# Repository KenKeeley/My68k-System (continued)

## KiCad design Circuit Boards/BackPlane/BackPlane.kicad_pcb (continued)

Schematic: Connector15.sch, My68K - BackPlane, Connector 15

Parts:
J15: DIN41612-C-96-F; Part No. 1656359
JP27, JP28: Jumper; Part No. 1593411

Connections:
+3V3: J15.A31, J15.B31, J15.C31; also elsewhere on the board
+5V: J15.A32, J15.B32, J15.C32; also elsewhere on the board
A00: J15.A23; also elsewhere on the board
A01: J15.A24; also elsewhere on the board
A02: J15.A25; also elsewhere on the board
A03: J15.A26; also elsewhere on the board
A04: J15.A27; also elsewhere on the board
A05: J15.A28; also elsewhere on the board
A06: J15.A29; also elsewhere on the board
A07: J15.A30; also elsewhere on the board
A08: J15.C23; also elsewhere on the board
A09: J15.C24; also elsewhere on the board
A10: J15.C25; also elsewhere on the board
A11: J15.C26; also elsewhere on the board
A12: J15.C27; also elsewhere on the board
A13: J15.C28; also elsewhere on the board
A14: J15.C29; also elsewhere on the board
A15: J15.C30; also elsewhere on the board
A16: J15.C11; also elsewhere on the board
A17: J15.C12; also elsewhere on the board
A18: J15.C13; also elsewhere on the board
A19: J15.C14; also elsewhere on the board
A20: J15.C15; also elsewhere on the board
A21: J15.C16; also elsewhere on the board
A22: J15.C17; also elsewhere on the board
A23: J15.C18; also elsewhere on the board
A24: J15.C19; also elsewhere on the board
A25: J15.A13; also elsewhere on the board
A26: J15.A14; also elsewhere on the board
A27: J15.A15; also elsewhere on the board
A28: J15.A16; also elsewhere on the board
A29: J15.A17; also elsewhere on the board
A30: J15.A18; also elsewhere on the board
A31: J15.A19; also elsewhere on the board
AS: J15.B9; also elsewhere on the board
BGACK: J15.A22; also elsewhere on the board
BGOUT14: J15.A20, JP27.1; also elsewhere on the board
BGOUT15: J15.A21, JP27.2; also elsewhere on the board
BR: J15.C22; also elsewhere on the board
D00: J15.A1; also elsewhere on the board
D01: J15.A2; also elsewhere on the board
D02: J15.A3; also elsewhere on the board
D03: J15.A4; also elsewhere on the board
D04: J15.A5; also elsewhere on the board
D05: J15.A6; also elsewhere on the board
D06: J15.A7; also elsewhere on the board
D07: J15.A8; also elsewhere on the board
D08: J15.C1; also elsewhere on the board
D09: J15.C2; also elsewhere on the board
D10: J15.C3; also elsewhere on the board
D11: J15.C4; also elsewhere on the board
D12: J15.C5; also elsewhere on the board
D13: J15.C6; also elsewhere on the board
D14: J15.C7; also elsewhere on the board
D15: J15.C8; also elsewhere on the board
D16: J15.B1; also elsewhere on the board
D17: J15.B2; also elsewhere on the board
D18: J15.B3; also elsewhere on the board
D19: J15.B4; also elsewhere on the board
D20: J15.B5; also elsewhere on the board
D21: J15.B6; also elsewhere on the board
D22: J15.B7; also elsewhere on the board
D23: J15.B8; also elsewhere on the board
D24: J15.B11; also elsewhere on the board
D25: J15.B12; also elsewhere on the board
D26: J15.B13; also elsewhere on the board
D27: J15.B14; also elsewhere on the board
D28: J15.B15; also elsewhere on the board
D29: J15.B16; also elsewhere on the board
D30: J15.B17; also elsewhere on the board
D31: J15.B18; also elsewhere on the board
DSACK0: J15.B22; also elsewhere on the board
DSACK1: J15.B23; also elsewhere on the board
GND: J15.33 (GND), J15.34 (GND), J15.A10, J15.B10, J15.C10; also elsewhere on the board
IACKOUT14: J15.B20, JP28.1; also elsewhere on the board
IACKOUT15: J15.B21, JP28.2; also elsewhere on the board
ID: J15.C21; also elsewhere on the board
IRQ1: J15.B30; also elsewhere on the board
IRQ2: J15.B29; also elsewhere on the board
IRQ3: J15.B28; also elsewhere on the board
IRQ4: J15.B27; also elsewhere on the board
IRQ5: J15.B26; also elsewhere on the board
IRQ6: J15.B25; also elsewhere on the board
IRQ7: J15.B24; also elsewhere on the board
SIZ0: J15.A11; also elsewhere on the board
SIZ1: J15.A12; also elsewhere on the board
STERM: J15.B19; also elsewhere on the board
SYSHALT: J15.C20; also elsewhere on the board
SYSRESET: J15.C9; also elsewhere on the board
WRITE: J15.A9; also elsewhere on the board

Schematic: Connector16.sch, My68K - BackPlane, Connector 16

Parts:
J16: DIN41612-C-96-F; Part No. 1656359

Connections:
+3V3: J16.A31, J16.B31, J16.C31; also elsewhere on the board
+5V: J16.A32, J16.B32, J16.C32; also elsewhere on the board
A00: J16.A23; also elsewhere on the board
A01: J16.A24; also elsewhere on the board
A02: J16.A25; also elsewhere on the board
A03: J16.A26; also elsewhere on the board
A04: J16.A27; also elsewhere on the board
A05: J16.A28; also elsewhere on the board
A06: J16.A29; also elsewhere on the board
A07: J16.A30; also elsewhere on the board
A08: J16.C23; also elsewhere on the board
A09: J16.C24; also elsewhere on the board
A10: J16.C25; also elsewhere on the board
A11: J16.C26; also elsewhere on the board
A12: J16.C27; also elsewhere on the board
A13: J16.C28; also elsewhere on the board
A14: J16.C29; also elsewhere on the board
A15: J16.C30; also elsewhere on the board
A16: J16.C11; also elsewhere on the board
A17: J16.C12; also elsewhere on the board
A18: J16.C13; also elsewhere on the board
A19: J16.C14; also elsewhere on the board
A20: J16.C15; also elsewhere on the board
A21: J16.C16; also elsewhere on the board
A22: J16.C17; also elsewhere on the board
A23: J16.C18; also elsewhere on the board
A24: J16.C19; also elsewhere on the board
A25: J16.A13; also elsewhere on the board
A26: J16.A14; also elsewhere on the board
A27: J16.A15; also elsewhere on the board
A28: J16.A16; also elsewhere on the board
A29: J16.A17; also elsewhere on the board
A30: J16.A18; also elsewhere on the board
A31: J16.A19; also elsewhere on the board
AS: J16.B9; also elsewhere on the board
BGACK: J16.A22; also elsewhere on the board
BGOUT15: J16.A20; also elsewhere on the board
BR: J16.C22; also elsewhere on the board
D00: J16.A1; also elsewhere on the board
D01: J16.A2; also elsewhere on the board
D02: J16.A3; also elsewhere on the board
D03: J16.A4; also elsewhere on the board
D04: J16.A5; also elsewhere on the board
D05: J16.A6; also elsewhere on the board
D06: J16.A7; also elsewhere on the board
D07: J16.A8; also elsewhere on the board
D08: J16.C1; also elsewhere on the board
D09: J16.C2; also elsewhere on the board
D10: J16.C3; also elsewhere on the board
D11: J16.C4; also elsewhere on the board
D12: J16.C5; also elsewhere on the board
D13: J16.C6; also elsewhere on the board
D14: J16.C7; also elsewhere on the board
D15: J16.C8; also elsewhere on the board
D16: J16.B1; also elsewhere on the board
D17: J16.B2; also elsewhere on the board
D18: J16.B3; also elsewhere on the board
D19: J16.B4; also elsewhere on the board
D20: J16.B5; also elsewhere on the board
D21: J16.B6; also elsewhere on the board
D22: J16.B7; also elsewhere on the board
D23: J16.B8; also elsewhere on the board
D24: J16.B11; also elsewhere on the board
D25: J16.B12; also elsewhere on the board
D26: J16.B13; also elsewhere on the board
D27: J16.B14; also elsewhere on the board
D28: J16.B15; also elsewhere on the board
D29: J16.B16; also elsewhere on the board
D30: J16.B17; also elsewhere on the board
D31: J16.B18; also elsewhere on the board
DSACK0: J16.B22; also elsewhere on the board
DSACK1: J16.B23; also elsewhere on the board
GND: J16.33 (GND), J16.34 (GND), J16.A10, J16.B10, J16.C10; also elsewhere on the board
IACKOUT15: J16.B20; also elsewhere on the board
ID: J16.C21; also elsewhere on the board
IRQ1: J16.B30; also elsewhere on the board
IRQ2: J16.B29; also elsewhere on the board
IRQ3: J16.B28; also elsewhere on the board
IRQ4: J16.B27; also elsewhere on the board
IRQ5: J16.B26; also elsewhere on the board
IRQ6: J16.B25; also elsewhere on the board
IRQ7: J16.B24; also elsewhere on the board
SIZ0: J16.A11; also elsewhere on the board
SIZ1: J16.A12; also elsewhere on the board
STERM: J16.B19; also elsewhere on the board
SYSHALT: J16.C20; also elsewhere on the board
SYSRESET: J16.C9; also elsewhere on the board
WRITE: J16.A9; also elsewhere on the board

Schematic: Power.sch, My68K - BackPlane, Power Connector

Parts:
J17: 4771 3-pin; 4771_3-pin; Part No. P5603
J18: DIN41612-H-15-F; Part No. 1656221

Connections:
+3V3: J18.D18 (3v), J18.Z16 (3v), J18.Z20 (3v); also elsewhere on the board
+5V: J18.D26 (5v), J18.Z24 (5v), J18.Z28 (5v); also elsewhere on the board
GND: J17.2, J18.33 (GND), J18.34 (GND), J18.D6 (GND), J18.D10 (GND), J18.D14 (GND), J18.D22 (GND), J18.D30 (GND); also elsewhere on the board
unnamed: J17.1, J18.Z8 (AC-L)
unnamed: J17.3, J18.Z4 (AC-N)
VTT: J18.Z12 (Vterm), J18.Z32 (Vterm); also elsewhere on the board

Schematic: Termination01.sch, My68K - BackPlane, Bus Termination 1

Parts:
C1, C2, C3: 39uF; CP_Radial_6.3x11x2.5; Part No. 2465934
RP1, RP2, RP3, RP4, RP5, RP6, RP7, RP8, RP9: 270; SIP_10; Part No. 1612547

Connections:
A00: RP7.3; also elsewhere on the board
A01: RP7.4; also elsewhere on the board
A02: RP7.5; also elsewhere on the board
A03: RP7.6; also elsewhere on the board
A04: RP7.7; also elsewhere on the board
A05: RP7.8; also elsewhere on the board
A06: RP7.9; also elsewhere on the board
A07: RP7.10; also elsewhere on the board
A08: RP9.3; also elsewhere on the board
A09: RP9.4; also elsewhere on the board
A10: RP9.5; also elsewhere on the board
A11: RP9.6; also elsewhere on the board
A12: RP9.7; also elsewhere on the board
A13: RP9.8; also elsewhere on the board
A14: RP9.9; also elsewhere on the board
A15: RP9.10; also elsewhere on the board
A16: RP6.10; also elsewhere on the board
A17: RP6.9; also elsewhere on the board
A18: RP6.8; also elsewhere on the board
A19: RP6.7; also elsewhere on the board
A20: RP6.6; also elsewhere on the board
A21: RP6.5; also elsewhere on the board
A22: RP6.4; also elsewhere on the board
A23: RP6.3; also elsewhere on the board
A24: RP6.2; also elsewhere on the board
A25: RP4.8; also elsewhere on the board
A26: RP4.7; also elsewhere on the board
A27: RP4.6; also elsewhere on the board
A28: RP4.5; also elsewhere on the board
A29: RP4.4; also elsewhere on the board
A30: RP4.3; also elsewhere on the board
A31: RP4.2; also elsewhere on the board
AS: RP2.10; also elsewhere on the board
BGACK: RP7.2; also elsewhere on the board
BR: RP9.2; also elsewhere on the board
D00: RP1.2; also elsewhere on the board
D01: RP1.3; also elsewhere on the board
D02: RP1.4; also elsewhere on the board
D03: RP1.5; also elsewhere on the board
D04: RP1.6; also elsewhere on the board
D05: RP1.7; also elsewhere on the board
D06: RP1.8; also elsewhere on the board
D07: RP1.9; also elsewhere on the board
D08: RP3.2; also elsewhere on the board
D09: RP3.3; also elsewhere on the board
D10: RP3.4; also elsewhere on the board
D11: RP3.5; also elsewhere on the board
D12: RP3.6; also elsewhere on the board
D13: RP3.7; also elsewhere on the board
D14: RP3.8; also elsewhere on the board
D15: RP3.9; also elsewhere on the board
D16: RP2.2; also elsewhere on the board
D17: RP2.3; also elsewhere on the board
D18: RP2.4; also elsewhere on the board
D19: RP2.5; also elsewhere on the board
D20: RP2.6; also elsewhere on the board
D21: RP2.7; also elsewhere on the board
D22: RP2.8; also elsewhere on the board
D23: RP2.9; also elsewhere on the board
D24: RP5.10; also elsewhere on the board
D25: RP5.9; also elsewhere on the board
D26: RP5.8; also elsewhere on the board
D27: RP5.7; also elsewhere on the board
D28: RP5.6; also elsewhere on the board
D29: RP5.5; also elsewhere on the board
D30: RP5.4; also elsewhere on the board
D31: RP5.3; also elsewhere on the board
DSACK0: RP8.2; also elsewhere on the board
DSACK1: RP8.3; also elsewhere on the board
GND: C1.2, C2.2, C3.2; also elsewhere on the board
IRQ1: RP8.10; also elsewhere on the board
IRQ2: RP8.9; also elsewhere on the board
IRQ3: RP8.8; also elsewhere on the board
IRQ4: RP8.7; also elsewhere on the board
IRQ5: RP8.6; also elsewhere on the board
IRQ6: RP8.5; also elsewhere on the board
IRQ7: RP8.4; also elsewhere on the board
SIZ0: RP4.10; also elsewhere on the board
SIZ1: RP4.9; also elsewhere on the board
STERM: RP5.2; also elsewhere on the board
SYSRESET: RP3.10; also elsewhere on the board
VTT: C1.1, C2.1, C3.1, RP1.1 (COM), RP2.1 (COM), RP3.1 (COM), RP4.1 (COM), RP5.1 (COM), RP6.1 (COM), RP7.1 (COM), RP8.1 (COM), RP9.1 (COM); also elsewhere on the board
WRITE: RP1.10; also elsewhere on the board

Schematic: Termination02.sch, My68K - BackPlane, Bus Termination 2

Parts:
C4, C5, C6: 39uF; CP_Radial_6.3x11x2.5; Part No. 2465934
RP11, RP12, RP13, RP14, RP15, RP16, RP17, RP18, RP19: 270; SIP_10; Part No. 1612547

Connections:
A00: RP17.3; also elsewhere on the board
A01: RP17.4; also elsewhere on the board
A02: RP17.5; also elsewhere on the board
A03: RP17.6; also elsewhere on the board
A04: RP17.7; also elsewhere on the board
A05: RP17.8; also elsewhere on the board
A06: RP17.9; also elsewhere on the board
A07: RP17.10; also elsewhere on the board
A08: RP19.3; also elsewhere on the board
A09: RP19.4; also elsewhere on the board
A10: RP19.5; also elsewhere on the board
A11: RP19.6; also elsewhere on the board
A12: RP19.7; also elsewhere on the board
A13: RP19.8; also elsewhere on the board
A14: RP19.9; also elsewhere on the board
A15: RP19.10; also elsewhere on the board
A16: RP16.10; also elsewhere on the board
A17: RP16.9; also elsewhere on the board
A18: RP16.8; also elsewhere on the board
A19: RP16.7; also elsewhere on the board
A20: RP16.6; also elsewhere on the board
A21: RP16.5; also elsewhere on the board
A22: RP16.4; also elsewhere on the board
A23: RP16.3; also elsewhere on the board
A24: RP16.2; also elsewhere on the board
A25: RP14.8; also elsewhere on the board
A26: RP14.7; also elsewhere on the board
A27: RP14.6; also elsewhere on the board
A28: RP14.5; also elsewhere on the board
A29: RP14.4; also elsewhere on the board
A30: RP14.3; also elsewhere on the board
A31: RP14.2; also elsewhere on the board
AS: RP12.10; also elsewhere on the board
BGACK: RP17.2; also elsewhere on the board
BR: RP19.2; also elsewhere on the board
D00: RP11.2; also elsewhere on the board
D01: RP11.3; also elsewhere on the board
D02: RP11.4; also elsewhere on the board
D03: RP11.5; also elsewhere on the board
D04: RP11.6; also elsewhere on the board
D05: RP11.7; also elsewhere on the board
D06: RP11.8; also elsewhere on the board
D07: RP11.9; also elsewhere on the board
D08: RP13.2; also elsewhere on the board
D09: RP13.3; also elsewhere on the board
D10: RP13.4; also elsewhere on the board
D11: RP13.5; also elsewhere on the board
D12: RP13.6; also elsewhere on the board
D13: RP13.7; also elsewhere on the board
D14: RP13.8; also elsewhere on the board
D15: RP13.9; also elsewhere on the board
D16: RP12.2; also elsewhere on the board
D17: RP12.3; also elsewhere on the board
D18: RP12.4; also elsewhere on the board
D19: RP12.5; also elsewhere on the board
D20: RP12.6; also elsewhere on the board
D21: RP12.7; also elsewhere on the board
D22: RP12.8; also elsewhere on the board
D23: RP12.9; also elsewhere on the board
D24: RP15.10; also elsewhere on the board
D25: RP15.9; also elsewhere on the board
D26: RP15.8; also elsewhere on the board
D27: RP15.7; also elsewhere on the board
D28: RP15.6; also elsewhere on the board
D29: RP15.5; also elsewhere on the board
D30: RP15.4; also elsewhere on the board
D31: RP15.3; also elsewhere on the board
DSACK0: RP18.2; also elsewhere on the board
DSACK1: RP18.3; also elsewhere on the board
GND: C4.2, C5.2, C6.2; also elsewhere on the board
IRQ1: RP18.10; also elsewhere on the board
IRQ2: RP18.9; also elsewhere on the board
IRQ3: RP18.8; also elsewhere on the board
IRQ4: RP18.7; also elsewhere on the board
IRQ5: RP18.6; also elsewhere on the board
IRQ6: RP18.5; also elsewhere on the board
IRQ7: RP18.4; also elsewhere on the board
SIZ0: RP14.10; also elsewhere on the board
SIZ1: RP14.9; also elsewhere on the board
STERM: RP15.2; also elsewhere on the board
SYSRESET: RP13.10; also elsewhere on the board
VTT: C4.1, C5.1, C6.1, RP11.1 (COM), RP12.1 (COM), RP13.1 (COM), RP14.1 (COM), RP15.1 (COM), RP16.1 (COM), RP17.1 (COM), RP18.1 (COM), RP19.1 (COM); also elsewhere on the board
WRITE: RP11.10; also elsewhere on the board

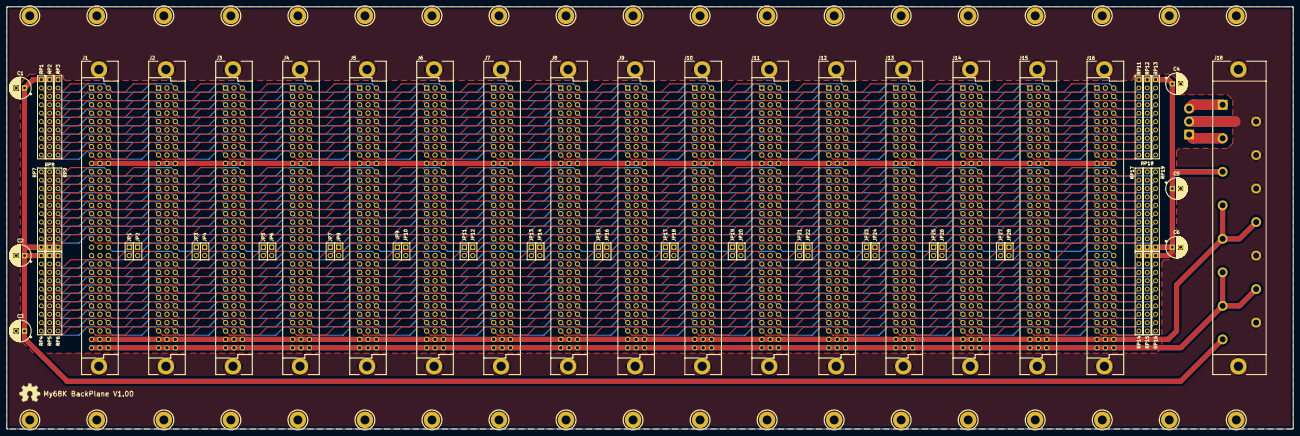
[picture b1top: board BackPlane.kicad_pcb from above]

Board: 4 copper layers, 390.0 x 128.0 mm, 72 parts (1 on the bottom side), 119 nets.

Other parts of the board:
LOGO: My68K BackPlane V1.00; OSHW_Logo

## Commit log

2019-01-26 Initial creation of the Project
2019-01-27 Addition of the system case
2019-01-27 Addition of the expansion card template
2019-01-28 Initial BackPlane creation
2019-02-16 Backplane: Initial PCB layout
2019-03-04 Initial PS card creation
